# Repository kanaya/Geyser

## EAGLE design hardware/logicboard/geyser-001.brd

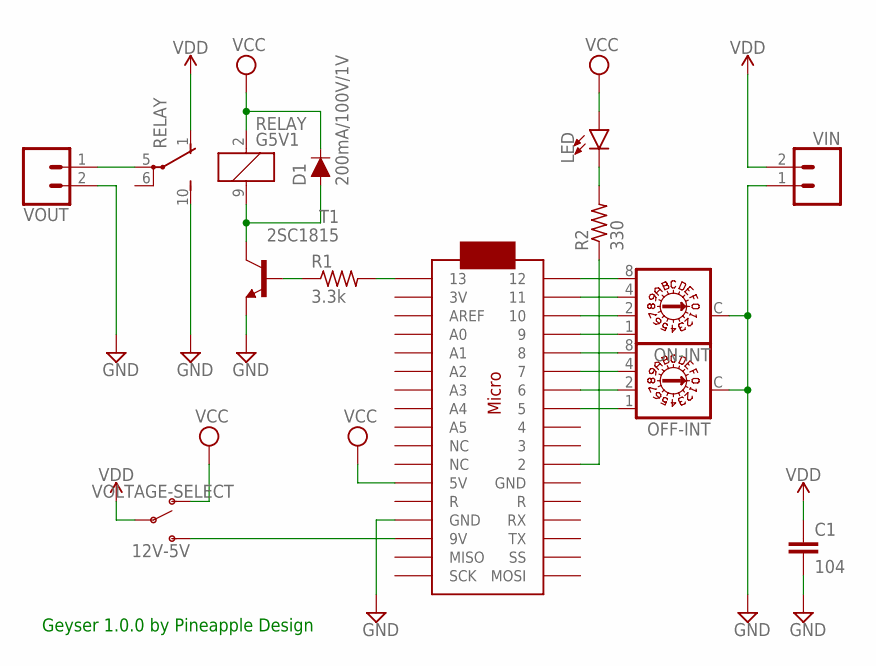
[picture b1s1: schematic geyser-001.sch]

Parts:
C1: 104; C2.5-3
D1: 200mA/100V/1V; DIODE-1N4148
LED: LED-3MM-NO_SILK; LED_3MM-NS
OFF-INT: A1353HEX
ON-INT: A1353HEX
R1: 3.3k; 0204/5
R2: 330; 0204/5
RELAY: G5V1
T1: 2SC1815; TO92-ECB
U$1: ARDUINOMICRO
VIN: CONN_02JST-PTH-2; JST-2-PTH
VOLTAGE-SELECT: 12V-5V; SWITCH_SPDT_PTH_11.6X4.0MM
VOUT: CONN_02JST-PTH-2; JST-2-PTH

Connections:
GND: C1.2, OFF-INT.C, ON-INT.C, RELAY.10 (S), T1.E, U$1.P$12 (GND), VIN.1, VOUT.2
LEDDRIVE: R2.1, U$1.P$11 (2)
unnamed: OFF-INT.8, U$1.P$5 (8)
unnamed: R1.1, T1.B
unnamed: D1.A, RELAY.9 (2), T1.C
unnamed: OFF-INT.4, U$1.P$6 (7)
unnamed: OFF-INT.2, U$1.P$7 (6)
unnamed: ON-INT.8, U$1.P$1 (12)
unnamed: ON-INT.4, U$1.P$2 (11)
unnamed: ON-INT.2, U$1.P$3 (10)
unnamed: ON-INT.1, U$1.P$4 (9)
unnamed: OFF-INT.1, U$1.P$8 (5)
unnamed: LED.K (C), R2.2
RELAYDRIVE: R1.2, U$1.P$34 (13)
VCC: D1.C, LED.A, RELAY.2 (1), U$1.P$23 (5V), VOLTAGE-SELECT.1 (O)
VDD: C1.1, RELAY.1 (O), VIN.2, VOLTAGE-SELECT.2
VIN: U$1.P$20 (9V), VOLTAGE-SELECT.3 (S)
VOUT: RELAY.5, VOUT.1

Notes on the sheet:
Geyser 1.0.0 by Pineapple Design

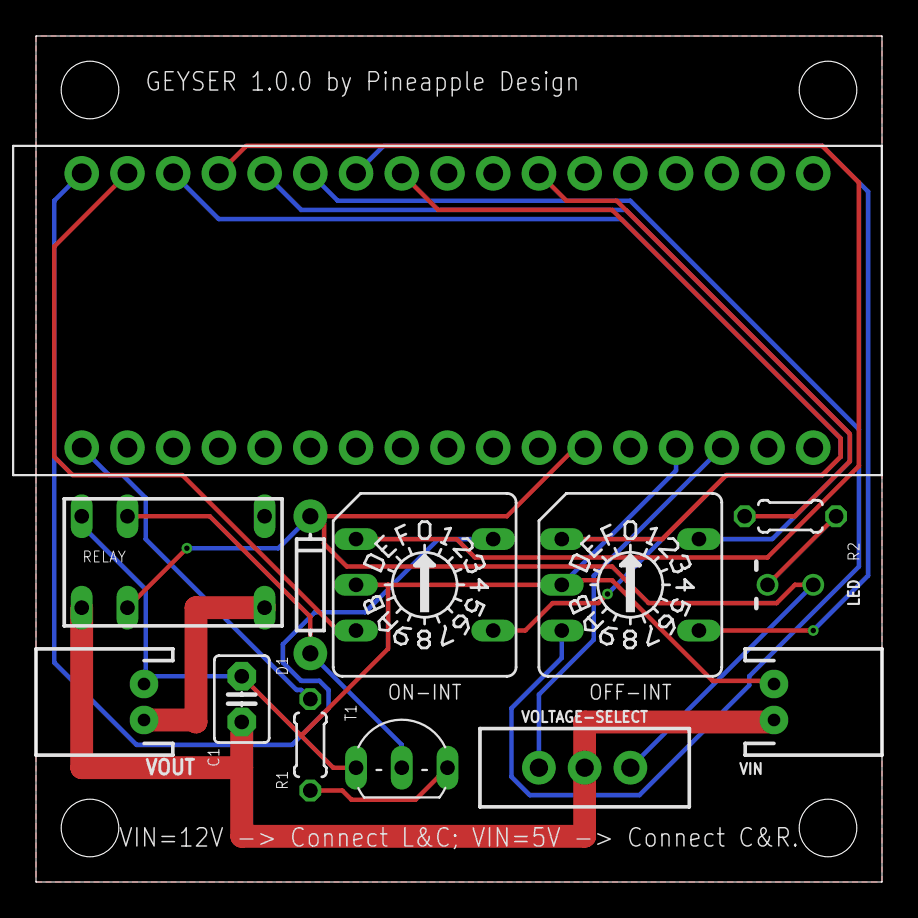
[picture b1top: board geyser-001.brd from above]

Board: 2 copper layers, 47.0 x 47.0 mm, 13 parts (0 on the bottom side), 18 nets.

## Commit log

2018-02-24 First try.
2018-02-26 Shrinked logicboard size.
2018-02-26 Test firmware.
2018-02-26 On and Off.
2018-02-27 Released firmware.
2018-02-27 Released hardware.
2018-02-27 Added capacitor.
2018-02-27 Changed configuration (a little bit.)
2018-02-28 Changed layout.
2018-02-28 GND.
2018-02-28 Name change.
2018-02-28 Fixed drill size.
2018-02-28 Design check.
2018-02-28 Image.
2018-02-28 Refined the board.
2018-02-28 Added silk.
2018-02-28 Changed pin layout.
2018-03-01 Changed copyright notice.
2018-03-02 Changed layout rule.
2018-03-02 CAM processed.
2018-03-02 Drill.
2018-03-02 New layout.
2018-03-02 P-ban files.
2018-03-09 Swapped + and -. Now + is on No.1 pin.
2018-03-09 Garber data.
2018-03-09 changed isolate of ratnest.
2018-03-09 Changed drill data.
2018-03-09 File list for p-ban.com.
2018-03-09 Added Makefile for making zip.
2018-03-09 Added comment.
2018-03-12 Refine.
2018-03-16 Changed silk pattern.
2018-03-16 Fixed missing silk pattern.

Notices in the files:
parts and their libraries:
SparkFun-Connectors: Licensing: Creative Commons ShareAlike 4.0 International - https://creativecommons.org/licenses/by-sa/4.0
